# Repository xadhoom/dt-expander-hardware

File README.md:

## Eagle schematics and board files for Detectino hardware

These are design files for two piggy back boards used in the Detectino Alarm project.

### Detectino_nodcdc
This is an expansion board used to read analog and digital inputs from commercial
alarm sensors and provide readings over a shared CAN bus.

The core is an Arduino Nano. The board provides protection for analog
and digital signals, in order to harden Arduino inputs and a CAN bus
transceiver.

Each board can handle 8 analog sensors and 3 digital ones.

Multiple boards can be connected over a single CAN bus.

### dt-expander-v2
An updated board based on Detectino_nodcdc, where the 3 digital input have been removed,
analog inputs increased from 8 to 16, 2 relays outputs have been added, along with
6 Open Collector outputs.

To accomodate all needed I/O, the board is plugged with an Arduino Mega2650 Pro Mini:
http://wiki.epalsite.com/index.php?title=Mega2560_Pro_Mini

### Detectino_raspi
This is the "core" board, which is a piggy back for RaspberryPi B+,
which provides isolated CAN bus and isolated power supply using
a suitable DC-DC converter.

The board is completely isolated from the environment, in order
to protect the RaspberryPi where the core software runs and
avoid disruption of the service caused by external electrical factors.

This board is plugged in the same CAN bus and communicate with
the Detection expansion boards-

#### Warning!
I'm not an electronic expert at all, so I tried to understand
and do my best in designing these boards.
If someone finds any error or have suggestions, please tell!

##### Notes
The other folders are initial design of the Arduino piggy back board,
not realized in practice.

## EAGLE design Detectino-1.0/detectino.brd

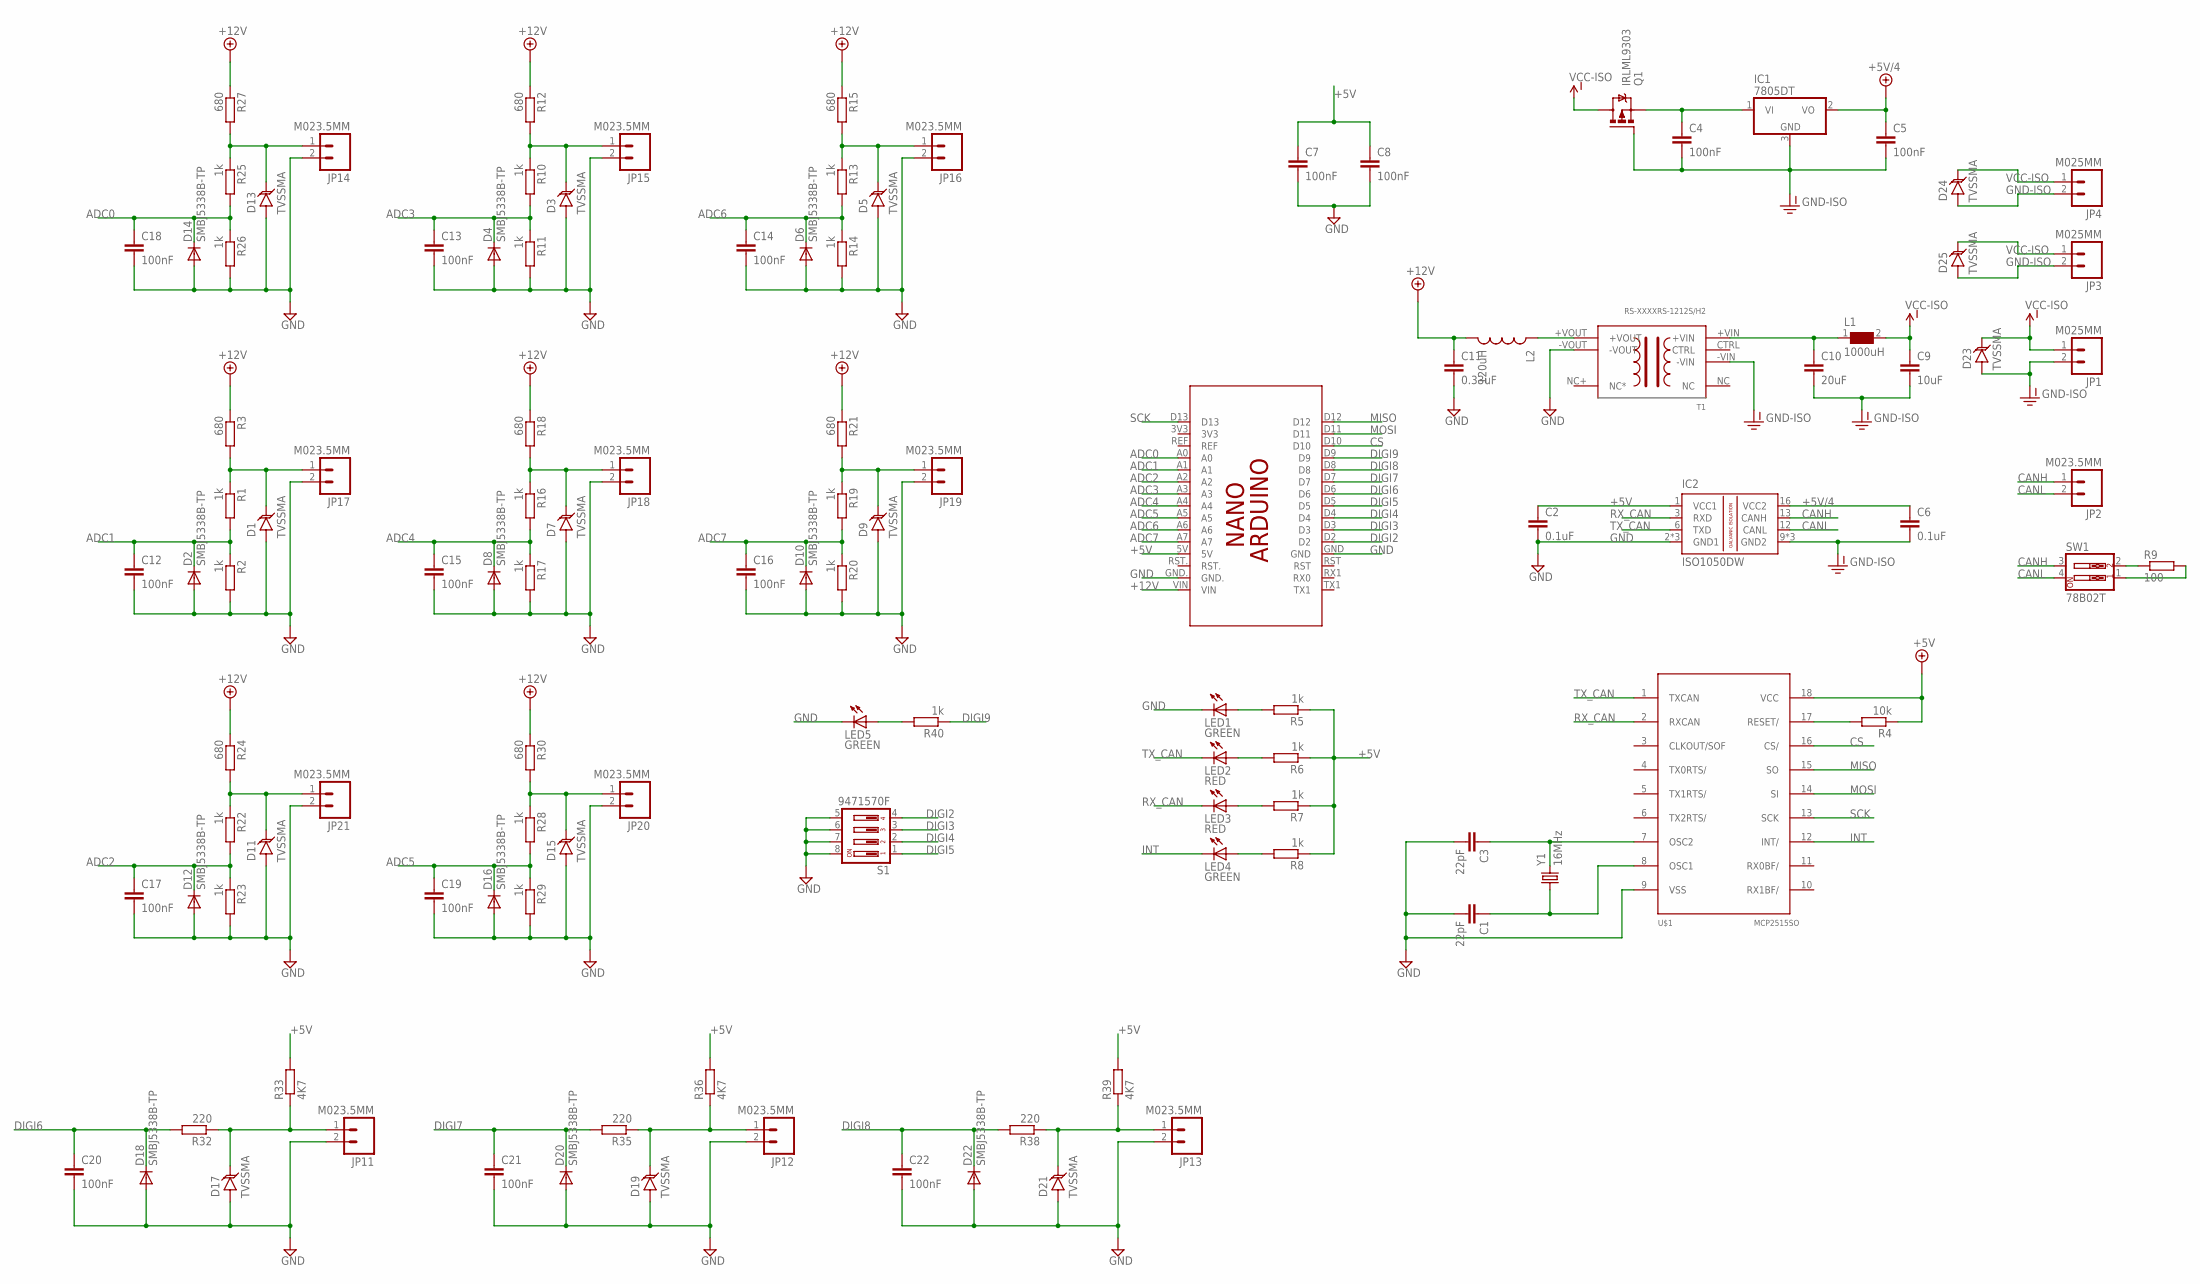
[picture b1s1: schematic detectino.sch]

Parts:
C1, C3: 22pF; C0805K
C2, C6: 0.1uF; C0805K
C4, C5, C7, C8, C12, C13, C14, C15, C16, C17, C18, C19, C20, C21, C22: 100nF; C0805K
C9: 10uF; C0805K
C10: 20uF; C0805K
C11: 0.33uF; C0805K
D1, D3, D5, D7, D9, D11, D13, D15, D17, D19, D21, D23, D24, D25: TVSSMA; SMA-DIODE
D2, D4, D6, D8, D10, D12, D14, D16, D18, D20, D22: SMBJ5338B-TP; DO214AA
IC1: 7805DT; TO252
IC2: ISO1050DW; SO-16DW
JP1, JP3, JP4: M025MM; SCREWTERMINAL-5MM-2
JP2, JP11, JP12, JP13, JP14, JP15, JP16, JP17, JP18, JP19, JP20, JP21: M023.5MM; SCREWTERMINAL-3.5MM-2
L1: 1000uH; WE-TIS_1111
L2: 120uH; SDR0403
LED1, LED4, LED5: GREEN; SML0805
LED2, LED3: RED; SML0805
PCB2: ARDUINO_NANO
Q1: IRLML9303; MICRO3
R1, R2, R5, R6, R7, R8, R10, R11, R13, R14, R16, R17, R19, R20, R22, R23, R25, R26, R28, R29, R40: 1k; 0204/5
R3, R12, R15, R18, R21, R24, R27, R30: 680; 0204/5
R4: 10k; R0805W
R9: 100; R0805W
R32, R35, R38: 220; 0204/5
R33, R36, R39: 4K7; 0204/5
S1: 9471570F; DS-04
SW1: 78B02T; DIPSWITCH-02
T1: RS-XXXXRS-1212S/H2; SIP8
U$1: MCP2515SO; SO18L
Y1: 16MHz; HC49US

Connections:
+5V: C2.1, C7.1, C8.1, IC2.1 (VCC1), PCB2.5V, R4.1, R5.1, R6.1, R7.1, R8.1, R33.2, R36.2, R39.2, U$1.18 (VCC)
+5V/4: C5.1, C6.1, IC1.2 (VO), IC2.16 (VCC2)
+12V: C11.1, L2.P$2 (2), PCB2.VIN, R3.1, R12.1, R15.1, R18.1, R21.1, R24.1, R27.1, R30.1
ADC0: C18.1, D14.C, PCB2.A0, R25.2, R26.1
ADC1: C12.1, D2.C, PCB2.A1, R1.2, R2.1
ADC2: C17.1, D12.C, PCB2.A2, R22.2, R23.1
ADC3: C13.1, D4.C, PCB2.A3, R10.2, R11.1
ADC4: C15.1, D8.C, PCB2.A4, R16.2, R17.1
ADC5: C19.1, D16.C, PCB2.A5, R28.2, R29.1
ADC6: C14.1, D6.C, PCB2.A6, R13.2, R14.1
ADC7: C16.1, D10.C, PCB2.A7, R19.2, R20.1
CANH: IC2.13 (CANH), JP2.1, SW1.3
CANL: IC2.12 (CANL), JP2.2, SW1.4
CS: PCB2.D10, U$1.16 (CS/)
DIGI2: PCB2.D2, S1.4
DIGI3: PCB2.D3, S1.3
DIGI4: PCB2.D4, S1.2
DIGI5: PCB2.D5, S1.1
DIGI6: C20.1, D18.C, PCB2.D6, R32.2
DIGI7: C21.1, D20.C, PCB2.D7, R35.2
DIGI8: C22.1, D22.C, PCB2.D8, R38.2
DIGI9: PCB2.D9, R40.1
GND: C1.2, C2.2, C3.2, C7.2, C8.2, C11.2, C12.2, C13.2, C14.2, C15.2, C16.2, C17.2, C18.2, C19.2, C20.2, C21.2, C22.2, D1.A, D2.A, D3.A, D4.A, D5.A, D6.A, D7.A, D8.A, D9.A, D10.A, D11.A, D12.A, D13.A, D14.A, D15.A, D16.A, D17.A, D18.A, D19.A, D20.A, D21.A, D22.A, IC2.2 (GND1), IC2.7 (GND1), IC2.8 (GND1), JP11.2, JP12.2, JP13.2, JP14.2, JP15.2, JP16.2, JP17.2, JP18.2, JP19.2, JP20.2, JP21.2, LED1.C, LED5.C, PCB2.GND, PCB2.GND., R2.2, R11.2, R14.2, R17.2, R20.2, R23.2, R26.2, R29.2, S1.5, S1.6, S1.7, S1.8, T1.-VOUT, U$1.9 (VSS)
GND-ISO: C4.2, C5.2, C6.2, C9.2, C10.2, D23.A, D24.A, D25.A, IC1.3 (GND), IC2.9 (GND2), IC2.10 (GND2), IC2.15 (GND2), JP1.2, JP3.2, JP4.2, Q1.1 (G), T1.-VIN
INT: LED4.C, U$1.12 (INT/)
MISO: PCB2.D12, U$1.15 (SO)
MOSI: PCB2.D11, U$1.14 (SI)
unnamed: D1.C, JP17.1, R1.1, R3.2
unnamed: R4.2, U$1.17 (RESET/)
unnamed: C1.1, U$1.8 (OSC1), Y1.1
unnamed: C3.1, U$1.7 (OSC2), Y1.2
unnamed: C4.1, IC1.1 (VI), Q1.2 (S)
unnamed: LED1.A, R5.2
unnamed: LED2.A, R6.2
unnamed: LED3.A, R7.2
unnamed: LED4.A, R8.2
unnamed: C10.1, L1.1, T1.+VIN
unnamed: R9.1, SW1.2
unnamed: R9.2, SW1.1
unnamed: D3.C, JP15.1, R10.1, R12.2
unnamed: D5.C, JP16.1, R13.1, R15.2
unnamed: D7.C, JP18.1, R16.1, R18.2
unnamed: D9.C, JP19.1, R19.1, R21.2
unnamed: D11.C, JP21.1, R22.1, R24.2
unnamed: D13.C, JP14.1, R25.1, R27.2
unnamed: D15.C, JP20.1, R28.1, R30.2
unnamed: L2.P$1 (1), T1.+VOUT
unnamed: D17.C, JP11.1, R32.1, R33.1
unnamed: D19.C, JP12.1, R35.1, R36.1
unnamed: D21.C, JP13.1, R38.1, R39.1
unnamed: LED5.A, R40.2
RX_CAN: IC2.3 (RXD), LED3.C, U$1.2 (RXCAN)
SCK: PCB2.D13, U$1.13 (SCK)
TX_CAN: IC2.6 (TXD), LED2.C, U$1.1 (TXCAN)
VCC-ISO: C9.1, D23.C, D24.C, D25.C, JP1.1, JP3.1, JP4.1, L1.2, Q1.3 (D)

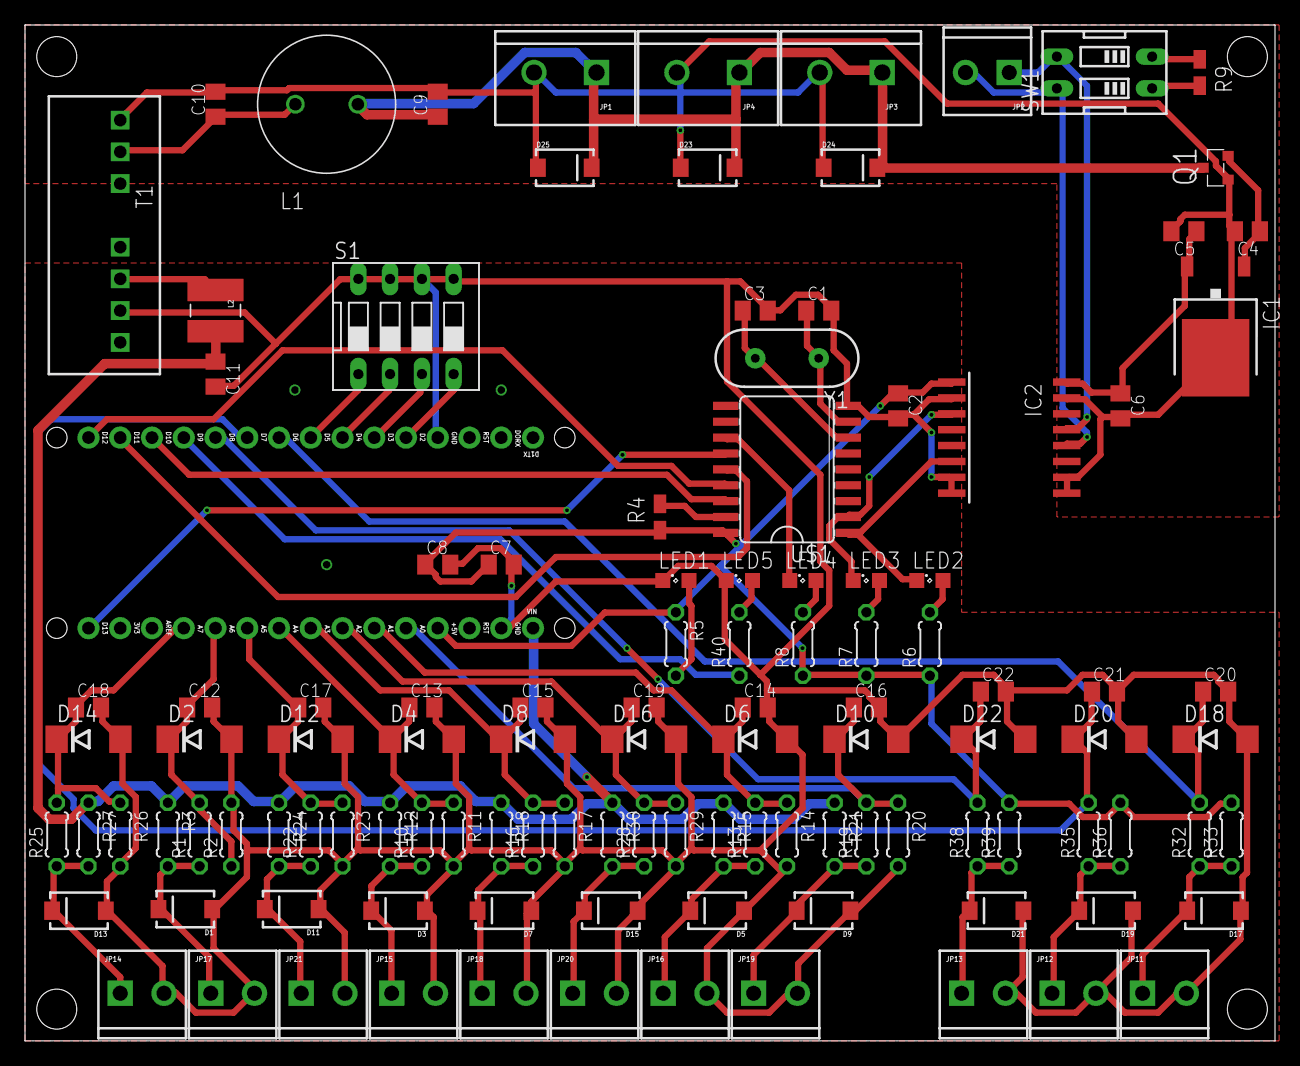
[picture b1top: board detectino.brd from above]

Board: 2 copper layers, 100.0 x 81.3 mm, 115 parts (0 on the bottom side), 55 nets.

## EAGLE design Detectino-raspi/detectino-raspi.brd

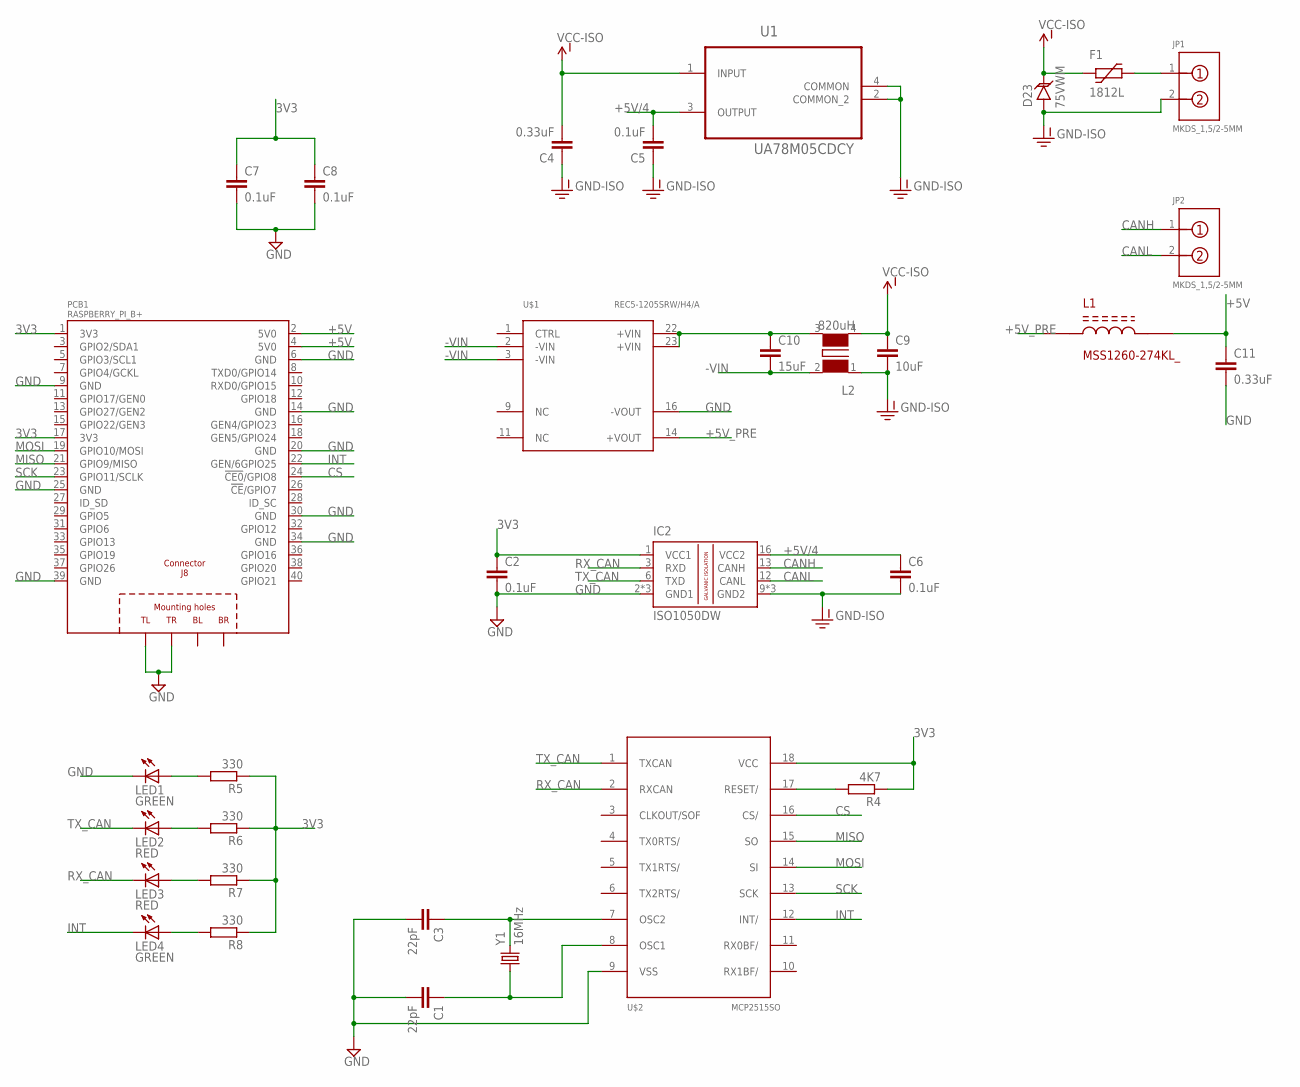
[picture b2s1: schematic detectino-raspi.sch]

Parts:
C1, C3: 22pF; C1206K
C2, C5, C6, C7, C8: 0.1uF; C1206K
C4, C11: 0.33uF; C1206K
C9: 10uF; C1812K
C10: 15uF; C1812K
D23: 75VWM; SMC
F1: 1812L
IC2: ISO1050DW; SO-16DW
JP1, JP2: MKDS_1,5/2-5MM
L1: MSS1260-274KL_; MSS1260
L2: 820uH; WE-FC_ET
LED1, LED4: GREEN; SML1206
LED2, LED3: RED; SML1206
PCB1: RASPBERRY_PI_B+
R4: 4K7; R1206
R5, R6, R7, R8: 330; R1206
U1: UA78M05CDCY; SOT230P700X180-4N
U$1: REC5-1205SRW/H4/A; DIP24
U$2: MCP2515SO; SO18L
Y1: 16MHz; HC49US

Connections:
3V3: C2.1, C7.1, C8.1, IC2.1 (VCC1), PCB1.1 (3V3), PCB1.17 (3V3), R4.1, R5.1, R6.1, R7.1, R8.1, U$2.18 (VCC)
+5V: C11.1, L1.P$2, PCB1.2 (5V0), PCB1.4 (5V0)
+5V/4: C5.2, C6.1, IC2.16 (VCC2), U1.3 (OUTPUT)
+5V_PRE: L1.P$1, U$1.14 (+VOUT)
+VIN: C10.1, L2.3, U$1.22 (+VIN), U$1.23 (+VIN)
-VIN: C10.2, L2.2 (4), U$1.2 (-VIN), U$1.3 (-VIN)
CANH: IC2.13 (CANH), JP2.1
CANL: IC2.12 (CANL), JP2.2
CS: PCB1.24 (!CE0!/GPIO8), U$2.16 (CS/)
GND: C1.2, C2.2, C3.2, C7.2, C8.2, C11.2, IC2.2 (GND1), IC2.7 (GND1), IC2.8 (GND1), LED1.C, PCB1.6 (GND), PCB1.9 (GND), PCB1.14 (GND), PCB1.20 (GND), PCB1.25 (GND), PCB1.30 (GND), PCB1.34 (GND), PCB1.39 (GND), PCB1.PE_TL (TL), PCB1.PE_TR (TR), U$1.16 (-VOUT), U$2.9 (VSS)
GND-ISO: C4.1, C5.1, C6.2, C9.2, D23.A, IC2.9 (GND2), IC2.10 (GND2), IC2.15 (GND2), JP1.2, L2.1, U1.2 (COMMON_2), U1.4 (COMMON)
INT: LED4.C, PCB1.22 (GEN/6GPIO25), U$2.12 (INT/)
MISO: PCB1.21 (GPIO9/MISO), U$2.15 (SO)
MOSI: PCB1.19 (GPIO10/MOSI), U$2.14 (SI)
unnamed: R4.2, U$2.17 (RESET/)
unnamed: C1.1, U$2.8 (OSC1), Y1.1
unnamed: C3.1, U$2.7 (OSC2), Y1.2
unnamed: F1.P$2 (2), JP1.1
unnamed: LED1.A, R5.2
unnamed: LED2.A, R6.2
unnamed: LED3.A, R7.2
unnamed: LED4.A, R8.2
RX_CAN: IC2.3 (RXD), LED3.C, U$2.2 (RXCAN)
SCK: PCB1.23 (GPIO11/SCLK), U$2.13 (SCK)
TX_CAN: IC2.6 (TXD), LED2.C, U$2.1 (TXCAN)
VCC-ISO: C4.2, C9.1, D23.C, F1.P$1 (1), L2.4 (2), U1.1 (INPUT)

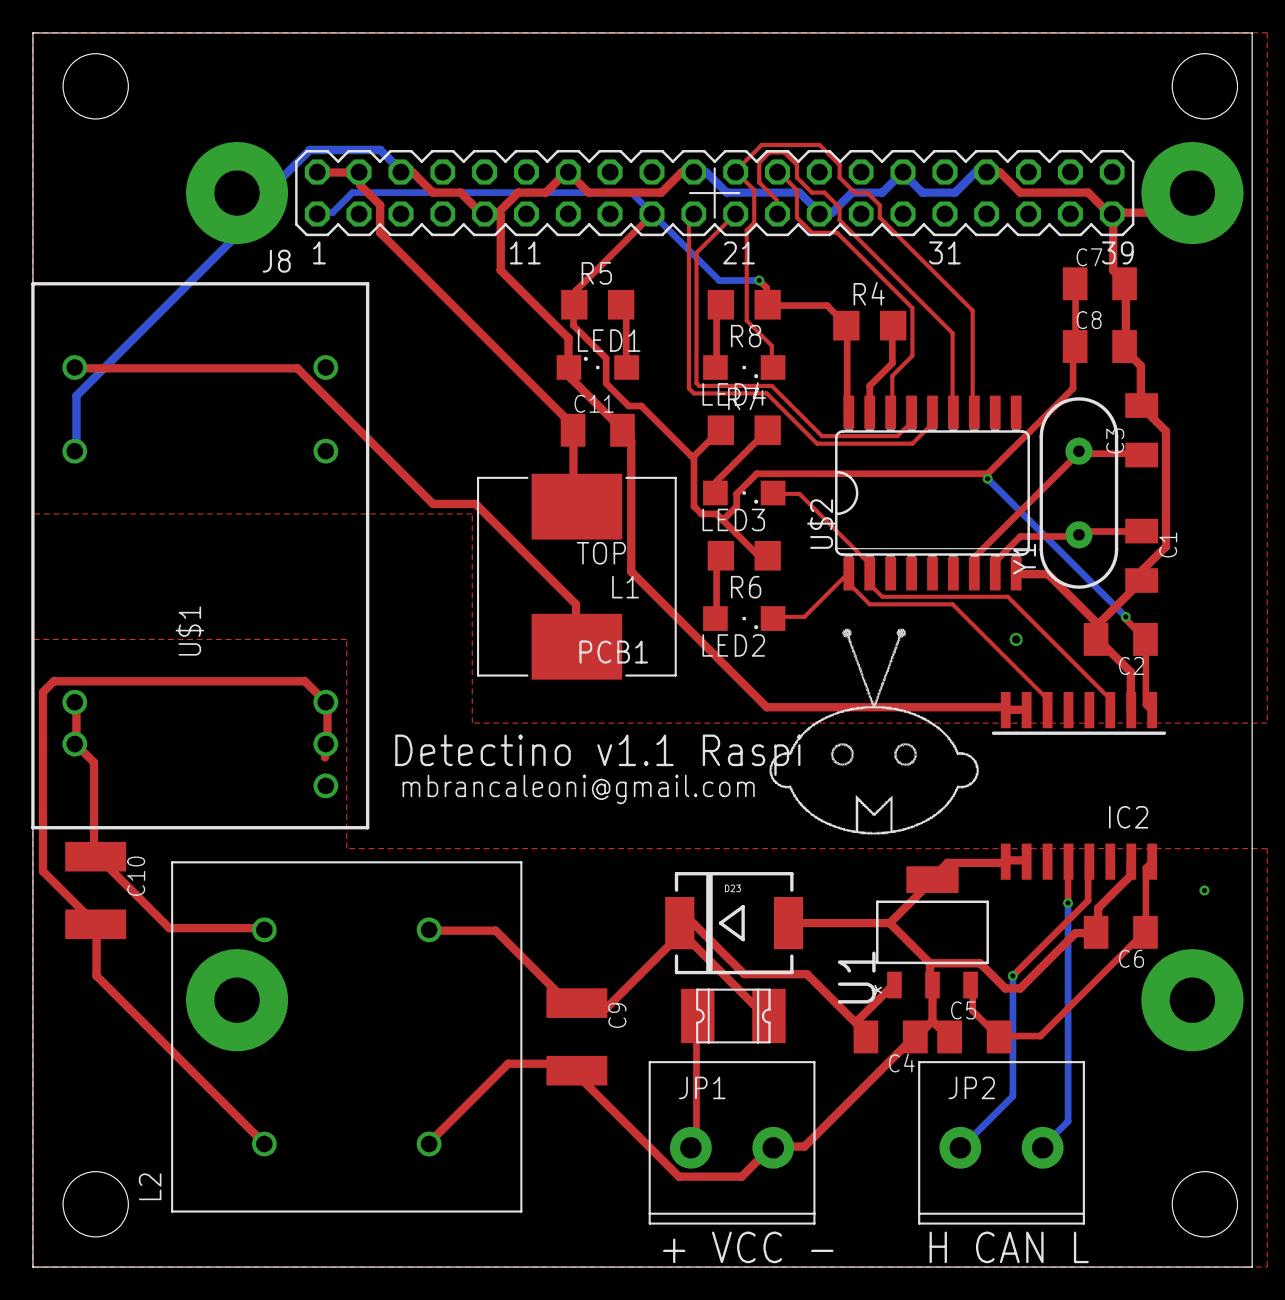
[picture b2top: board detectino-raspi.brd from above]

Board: 2 copper layers, 74.0 x 74.9 mm, 33 parts (0 on the bottom side), 26 nets.

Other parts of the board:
U$6: LOGO

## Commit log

2015-10-18 initial import
2015-10-18 more updates to readme
2017-10-15 kicad files for new board with 16 inputs, 2 relays and 6 open collectors outputs

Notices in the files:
parts and their libraries:
SparkFun-Connectors: Licensing: Creative Commons ShareAlike 4.0 International - https://creativecommons.org/licenses/by-sa/4.0
